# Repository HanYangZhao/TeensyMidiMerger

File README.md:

# TeensyMidiMerger
Teensy 3.6 bases USB midi merger

Merges midi signal from 4 USB midi devices (using midi host) and outputs via 1 standard midi port as well as teensy usb out

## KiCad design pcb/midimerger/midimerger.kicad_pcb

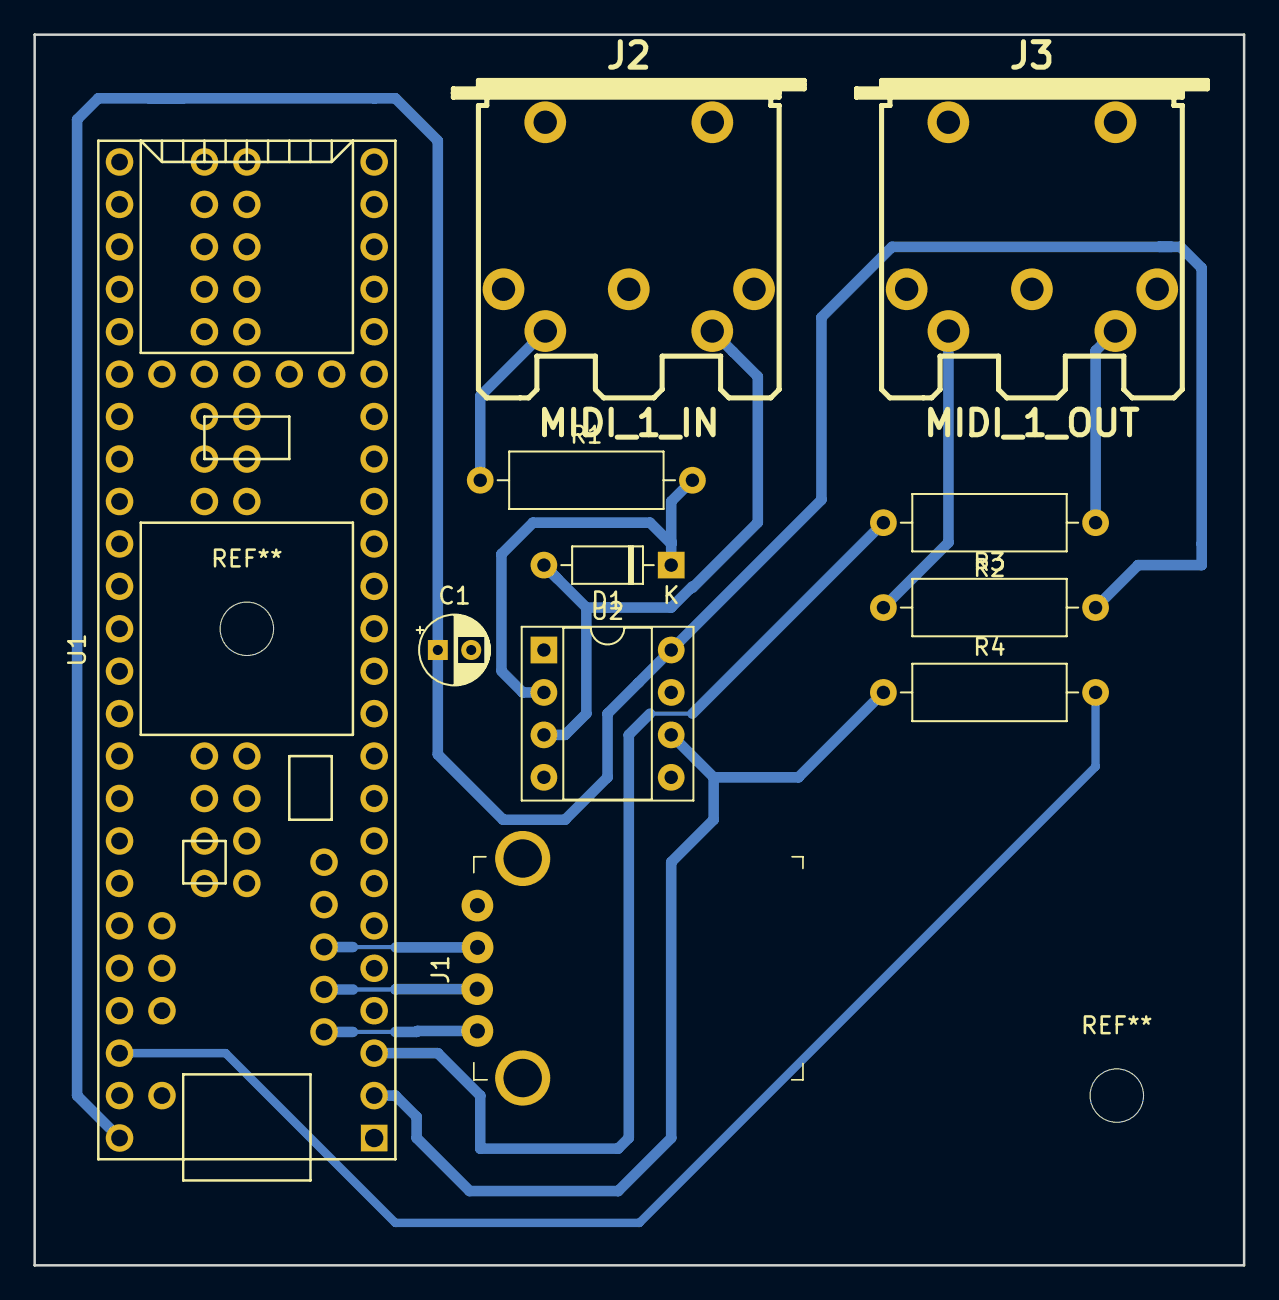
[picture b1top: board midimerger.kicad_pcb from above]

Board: 2 copper layers, 72.4 x 73.7 mm, 11 parts (0 on the bottom side), 14 nets.

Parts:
C1: 0.1uf; CP_Radial_D4.0mm_P2.00mm
D1: 1N4148; D_DO-35_SOD27_P7.62mm_Horizontal
J1: USB_A; USB_A_Female_UE27AC54100
J2: MIDI_1_IN; MIDI_DIN5
J3: MIDI_1_OUT; MIDI_DIN5
R1, R2, R3: 220; R_Axial_DIN0309_L9.0mm_D3.2mm_P12.70mm_Horizontal
R4: 470; R_Axial_DIN0309_L9.0mm_D3.2mm_P12.70mm_Horizontal
U1: Teensy3.6; Teensy35_36
U2: 6N138; DIP-8_W7.62mm_Socket

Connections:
/3.3V: R4.2, U1.51
/5V: R3.2, U1.53
/H_USB_5V: J1.1, U1.58
/H_USB_D+: J1.3, U1.60
/H_USB_D-: J1.2, U1.59
/MIDI_1_IN: R4.1, U1.2, U2.6
/MIDI_1_OUT: R2.2, U1.3
GND: C1.2, J1.4, J2.2, J3.2, U1.1, U1.27, U1.61, U1.62, U2.5
unnamed: C1.1, U2.8
unnamed: D1.1, R1.2, U2.2
unnamed: D1.2, J2.5, U2.3
unnamed: J2.4, R1.1
unnamed: J3.4, R3.1
unnamed: J3.5, R2.1

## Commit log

2019-01-13 initial code commit
2019-01-14 updated velocity for volca fm
2019-01-17 started pcb
2019-01-17 Added digikey
2019-01-17 removed src
2019-01-22 updated pcb
2019-01-24 diabled midi play/stop/continue
2019-01-24 made trace thicker
2019-01-24 fixed typo
2019-01-25 added export
2019-01-25 added mask
2019-01-26 increased teensy pad size
2019-01-27 added midi in
2019-01-27 fixed pcb ground and pull up voltage
2019-01-27 update schematics
2019-01-29 added new photos
2019-02-01 fixed 5v
